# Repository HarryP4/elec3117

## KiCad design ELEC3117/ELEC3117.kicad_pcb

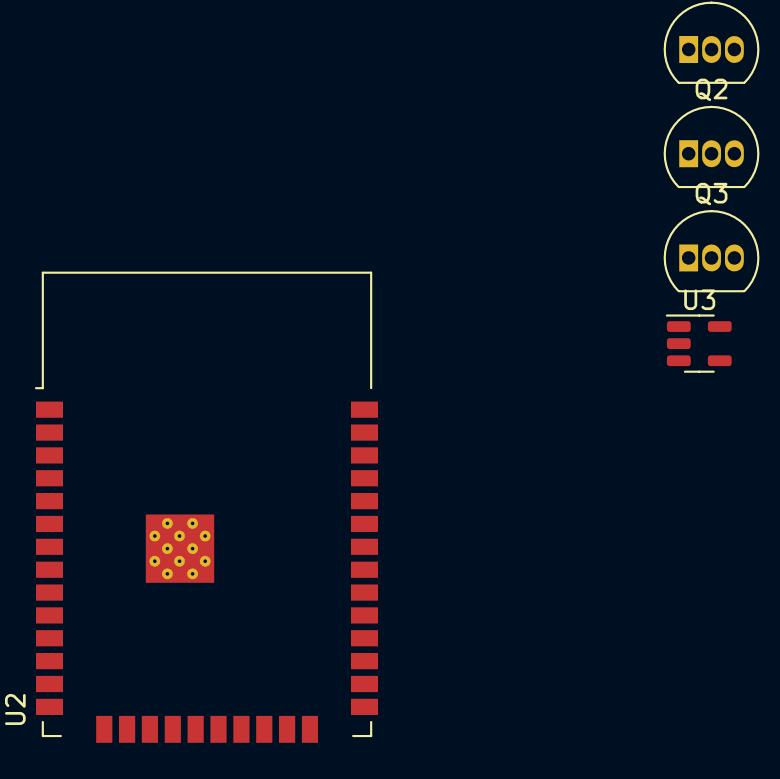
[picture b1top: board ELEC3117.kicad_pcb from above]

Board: 2 copper layers, 5 parts (0 on the bottom side), 7 nets, no tracks yet.

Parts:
Q1, Q2, Q3: BC550; TO-92_Inline
U2: ESP32-WROOM-32D
U3: MCP73831-2-OT; SOT-23-5

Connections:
+BATT: Q3.1 (C), U3.3 (V_{BAT})
-BATT: U2.1 (GND), U2.15 (GND), U2.38 (GND), U2.39 (GND), U3.2 (V_{SS})
unnamed: Q1.2 (B), U2.7 (IO35)
unnamed: Q1.1 (C), U3.5 (PROG)
unnamed: Q2.2 (B), U3.4 (V_{DD})
unnamed: Q2.1 (C), U2.2 (VDD)
unnamed: Q2.3 (E), U2.9 (IO33)

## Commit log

2023-07-03 init commit
